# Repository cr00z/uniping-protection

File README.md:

# uniping-protection
Защита для устройств Uniping v.3 (длинные линии). Архив проекта.

Может когда-нибудь нужно будет собрать еще 1-2 устройство. Если не нужно что-то менять, можно печатать сразу из pdf.

В папке old - предыдущая версия, скорее всего - шлак.

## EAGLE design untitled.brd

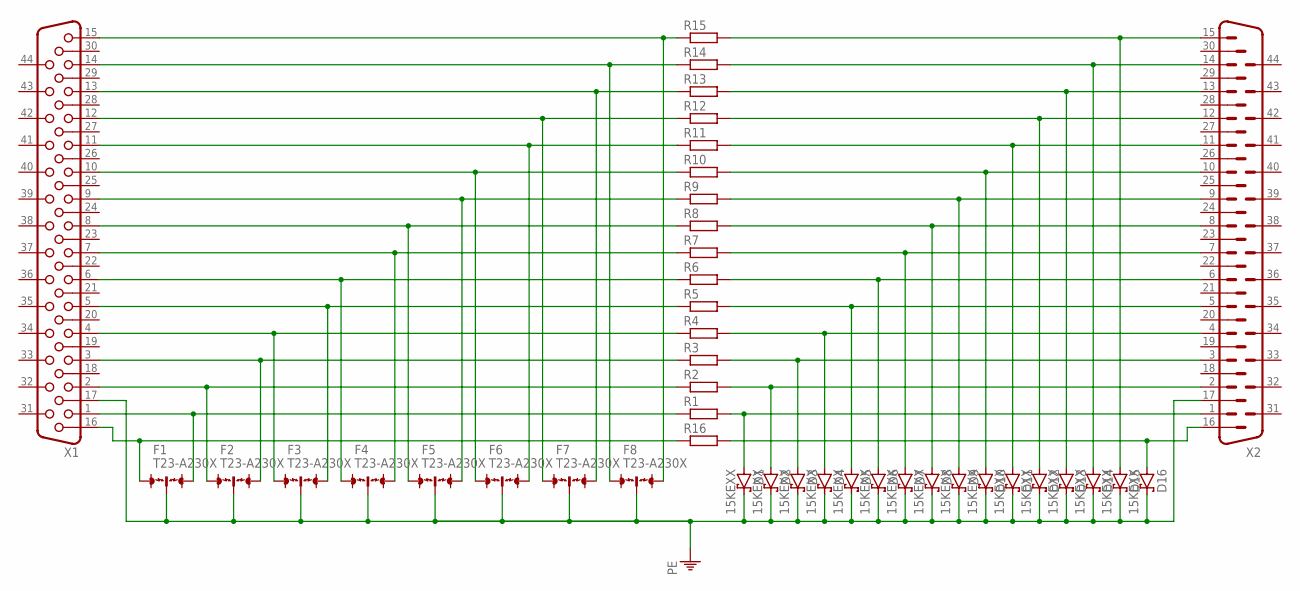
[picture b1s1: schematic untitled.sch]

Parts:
D1, D2, D3, D4, D5, D6, D7, D8, D9, D10, D11, D12, D13, D14, D15, D16: 15KEXX; CB429-17
F1, F2, F3, F4, F5, F6, F7, F8: T23-A230X
R1, R2, R3, R4, R5, R6, R7, R8, R9, R10, R11, R12, R13, R14, R15, R16: R-EU_R1210; R1210
X1: HF44H; HDF44H
X2: HM44H; HDM44H

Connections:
unnamed: D16.A, R16.2, X2.16
unnamed: D1.A, R1.2, X2.1
unnamed: D2.A, R2.2, X2.2
unnamed: D3.A, R3.2, X2.3
unnamed: D4.A, R4.2, X2.4
unnamed: D5.A, R5.2, X2.5
unnamed: D6.A, R6.2, X2.6
unnamed: D7.A, R7.2, X2.7
unnamed: D8.A, R8.2, X2.8
unnamed: D9.A, R9.2, X2.9
unnamed: D10.A, R10.2, X2.10
unnamed: D11.A, R11.2, X2.11
unnamed: D12.A, R12.2, X2.12
unnamed: D13.A, R13.2, X2.13
unnamed: D14.A, R14.2, X2.14
unnamed: F1.3, R1.1, X1.1
unnamed: F2.1, R2.1, X1.2
unnamed: F2.3, R3.1, X1.3
unnamed: F3.1, R4.1, X1.4
unnamed: F3.3, R5.1, X1.5
unnamed: F4.1, R6.1, X1.6
unnamed: F4.3, R7.1, X1.7
unnamed: F5.1, R8.1, X1.8
unnamed: F5.3, R9.1, X1.9
unnamed: F6.1, R10.1, X1.10
unnamed: F6.3, R11.1, X1.11
unnamed: F7.1, R12.1, X1.12
unnamed: F7.3, R13.1, X1.13
unnamed: F8.1, R14.1, X1.14
unnamed: F8.3, R15.1, X1.15
unnamed: F1.1, R16.1, X1.16
unnamed: D15.A, R15.2, X2.15
PE: D1.C, D2.C, D3.C, D4.C, D5.C, D6.C, D7.C, D8.C, D9.C, D10.C, D11.C, D12.C, D13.C, D14.C, D15.C, D16.C, F1.2, F2.2, F3.2, F4.2, F5.2, F6.2, F7.2, F8.2, X1.17, X2.17

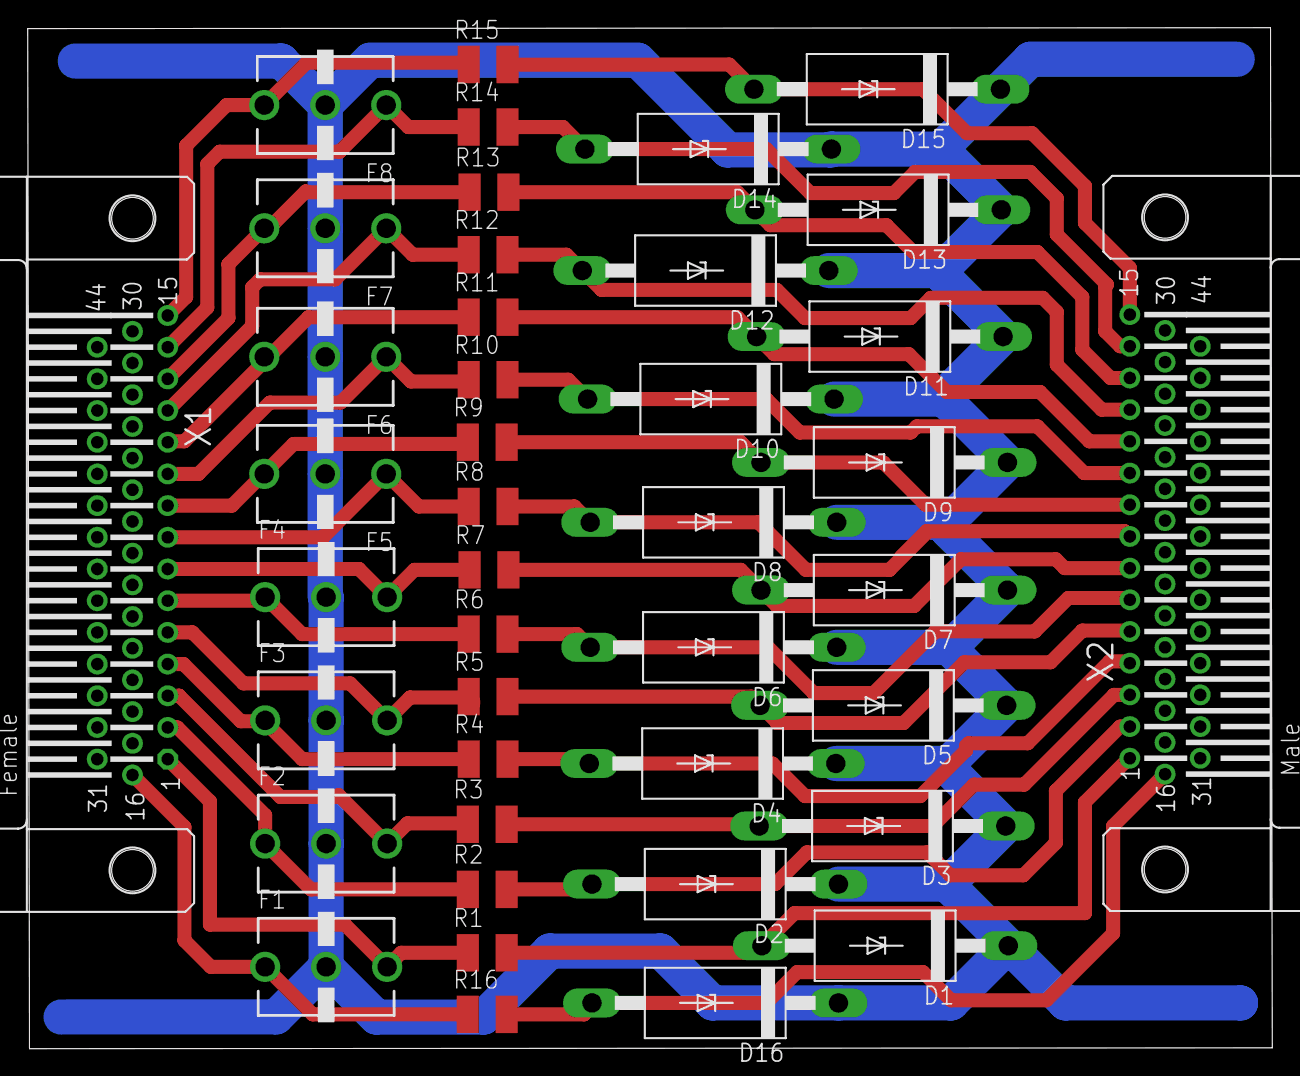
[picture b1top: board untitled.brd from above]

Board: 2 copper layers, 89.8 x 73.7 mm, 42 parts (0 on the bottom side), 33 nets.
